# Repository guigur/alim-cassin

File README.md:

# alim-cassin
## Présentation
Ce PCB est un shield pour Arduino UNO.

Son but principal est de fournir à partir d'une batterie externe un rail **7V** très propre au régulateur linéaire de l'Arduino tout en générant également une alimentation **5V** pour alimenter un servomoteur. L'alimentation externe peut être coupée du système grâce au connecteur JST-XH3 où un bouton d'arrêt d'urgent NC se doit être connecté.

En découplant les alimentations, cela évite les resets intempestifs de l'Arduino lors d'efforts du servomoteur.

La version 2 du montage dispose d'un connecteur JST-XH4 compatible Groove afin d'y connecter un périphérique externe (dans notre cas un module bluetooth).
Un pont diviseur de tension est connecté sur le pin A0 permet également de mesurer la tension d'entrée jusqu'à 14V.

Enfin des LEDs permettent de visualiser l'état des rails d'alimentation.

## Schéma électrique

## Rendu 3D

## Le PCB (Prototype)

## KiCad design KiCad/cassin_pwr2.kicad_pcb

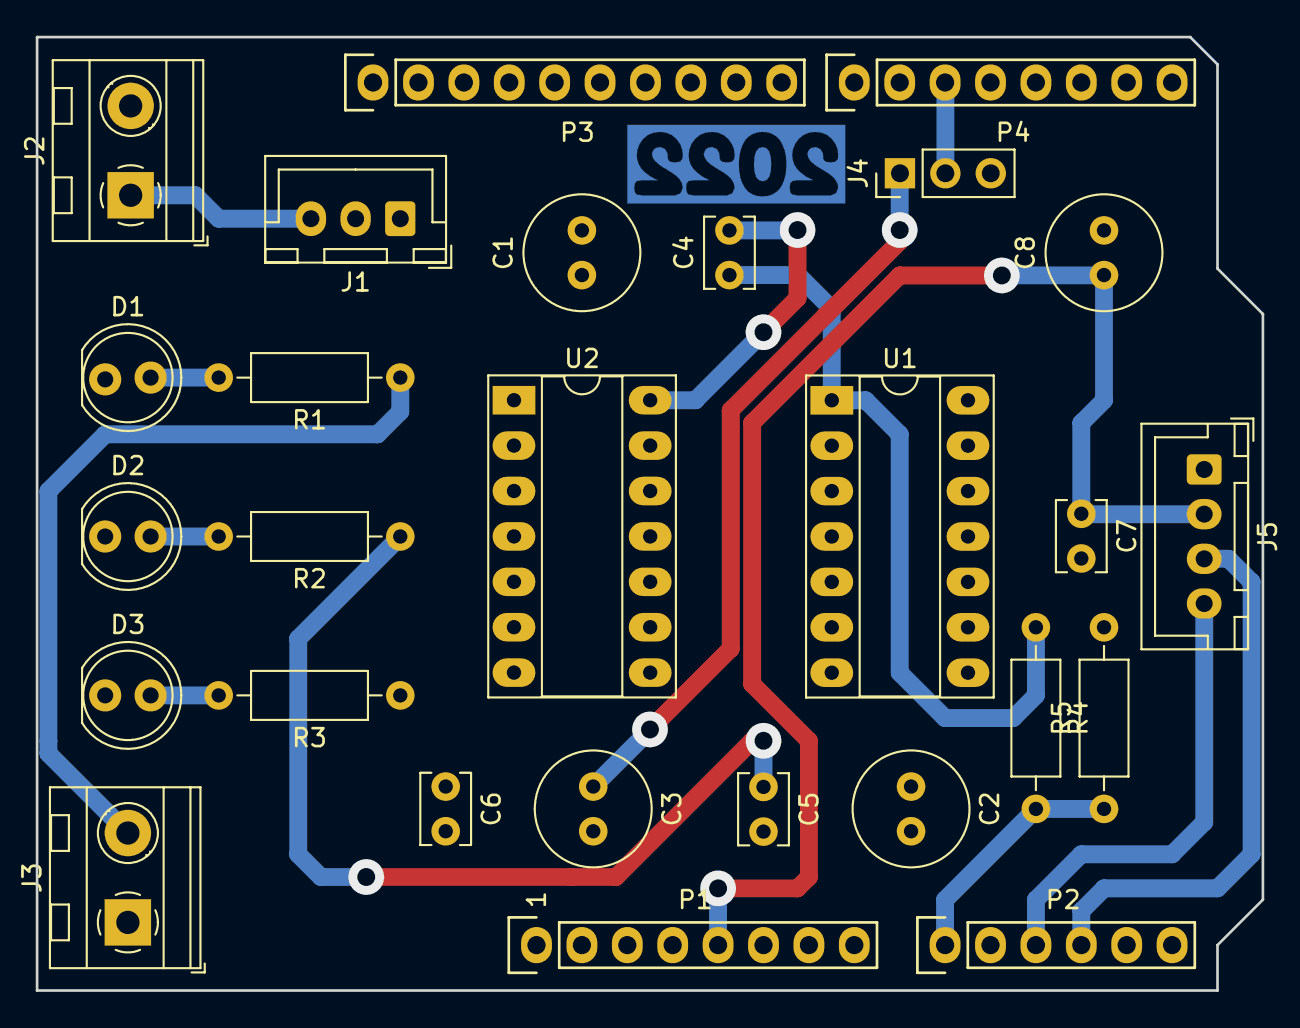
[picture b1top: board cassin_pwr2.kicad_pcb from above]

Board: 2 copper layers, 68.6 x 53.3 mm, 28 parts (1 on the bottom side), 15 nets.

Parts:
C1, C2, C3, C8: 470uF; C_Radial_D6.3mm_H11.0mm_P2.50mm
C4, C5, C6, C7: 100nF; C_Disc_D3.8mm_W2.6mm_P2.50mm
D1, D2, D3: LED; LED_D5.0mm
J1: Conn_01x03_Male; JST_XH_B3B-XH-A_1x03_P2.50mm_Vertical
J2, J3: Screw_Terminal_01x02; TerminalBlock_MetzConnect_Type094_RT03502HBLU_1x02_P5.00mm_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
J4: Conn_01x03_Male; PinHeader_1x03_P2.54mm_Vertical
J5: Conn_01x04_Male; JST_XH_B4B-XH-A_1x04_P2.50mm_Vertical
P1: Power; Socket_Strip_Arduino_1x08
P2: Analog; Socket_Strip_Arduino_1x06
P3: Digital; Socket_Strip_Arduino_1x10
P4: Digital; Socket_Strip_Arduino_1x08
R1, R2, R3, R4, R5: R; R_Axial_DIN0207_L6.3mm_D2.5mm_P10.16mm_Horizontal
U1, U2: mini360; DIP-14_W7.62mm_Socket_LongPads
kibuzzard-628A722A: G***; kibuzzard-628A722A

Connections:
+5V: C7.1, C8.1, J5.2, P1.5
/5(**): J4.2, P4.3
/A0: P2.1, R4.2, R5.1
/A2: J5.4, P2.3
/A3: J5.3, P2.4
/A4(SDA): P2.5, P3.2
/A5(SCL): P2.6, P3.1
/Vin: C2.1, C5.1, P1.8, R2.1, U1.7 (VOUT)
/Vmot: C1.1, C4.1, J1.1, J3.2, R1.1, R4.1, U1.1 (VIN), U2.1 (VIN)
/Vservo: C3.1, C6.1, J4.1, R3.1, U2.7 (VOUT)
GND: C1.2, C2.2, C3.2, C4.2, C5.2, C6.2, C7.2, C8.2, D1.1 (K), D2.1 (K), D3.1 (K), J2.2, J3.1, J4.3, J5.1, P1.6, P1.7, P3.4, R5.2, U1.2 (GND), U1.3 (GND), U1.4 (GND), U1.5 (GND), U1.6 (GND), U1.8 (GND), U1.9 (GND), U1.10 (GND), U1.11 (GND), U1.12 (GND), U1.13 (GND), U1.14 (GND), U2.2 (GND), U2.3 (GND), U2.4 (GND), U2.5 (GND), U2.6 (GND), U2.8 (GND), U2.9 (GND), U2.10 (GND), U2.11 (GND), U2.12 (GND), U2.13 (GND), U2.14 (GND)
unnamed: D1.2 (A), R1.2
unnamed: D2.2 (A), R2.2
unnamed: D3.2 (A), R3.2
unnamed: J1.3, J2.1

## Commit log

2022-05-21 first version
2022-05-22 v0.3
2022-05-30 fabversion
2022-06-02 added images
